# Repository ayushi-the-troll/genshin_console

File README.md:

# Genshin Impact Console
I've been wanting to create a console for my favorite game: Genshin Impact. For me, the keys on a keyboard are finnicky and too small for me to navigate them well. That's why I created a separate console that I can use for the game.

It can also be programmed for other games on PC that use the keyboard to perform actions. It has up to five action-buttons that you can use!

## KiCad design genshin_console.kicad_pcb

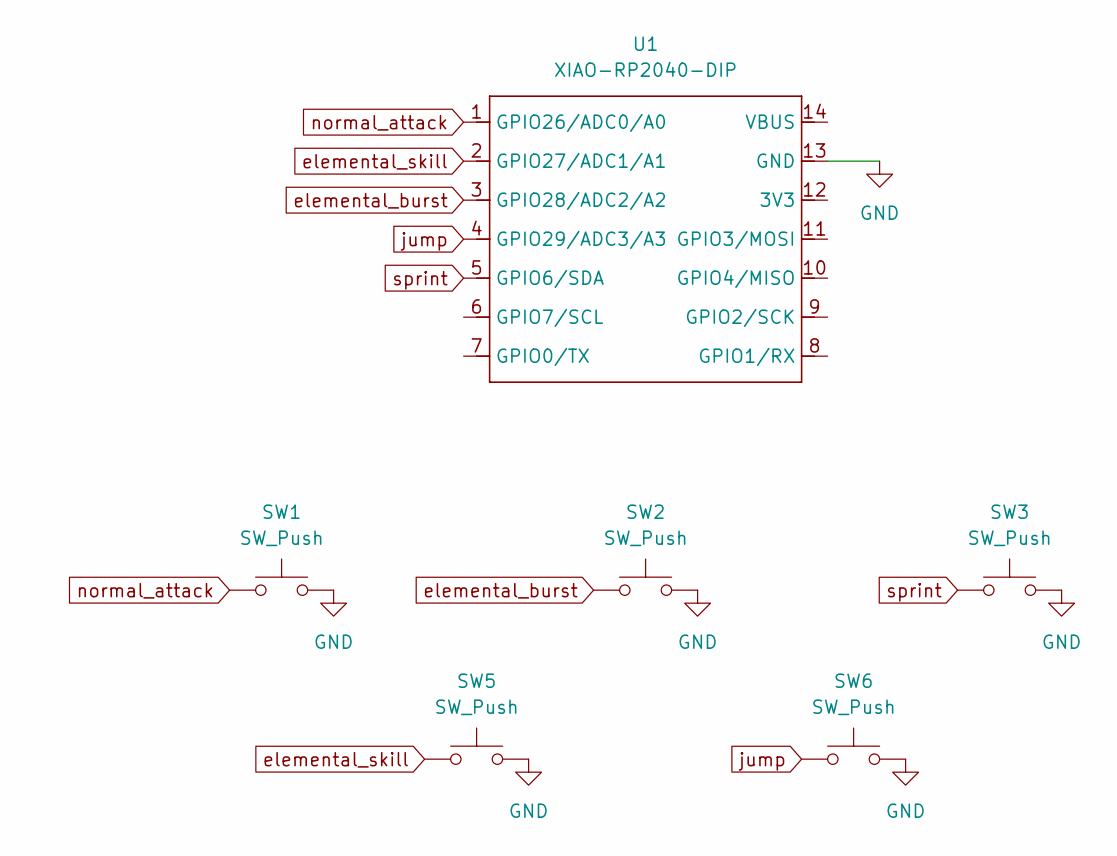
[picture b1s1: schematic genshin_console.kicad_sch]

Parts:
SW1, SW2, SW3, SW5, SW6: SW_Push; SW_Cherry_MX_1.00u_PCB
U1: XIAO-RP2040-DIP; XIAO-RP2040-DIP (1)

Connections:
GND: SW1.2, SW2.2, SW3.2, SW5.2, SW6.2, U1.13 (GND)
elemental_burst: SW2.1, U1.3 (GPIO28/ADC2/A2)
elemental_skill: SW5.1, U1.2 (GPIO27/ADC1/A1)
jump: SW6.1, U1.4 (GPIO29/ADC3/A3)
normal_attack: SW1.1, U1.1 (GPIO26/ADC0/A0)
sprint: SW3.1, U1.5 (GPIO6/SDA)

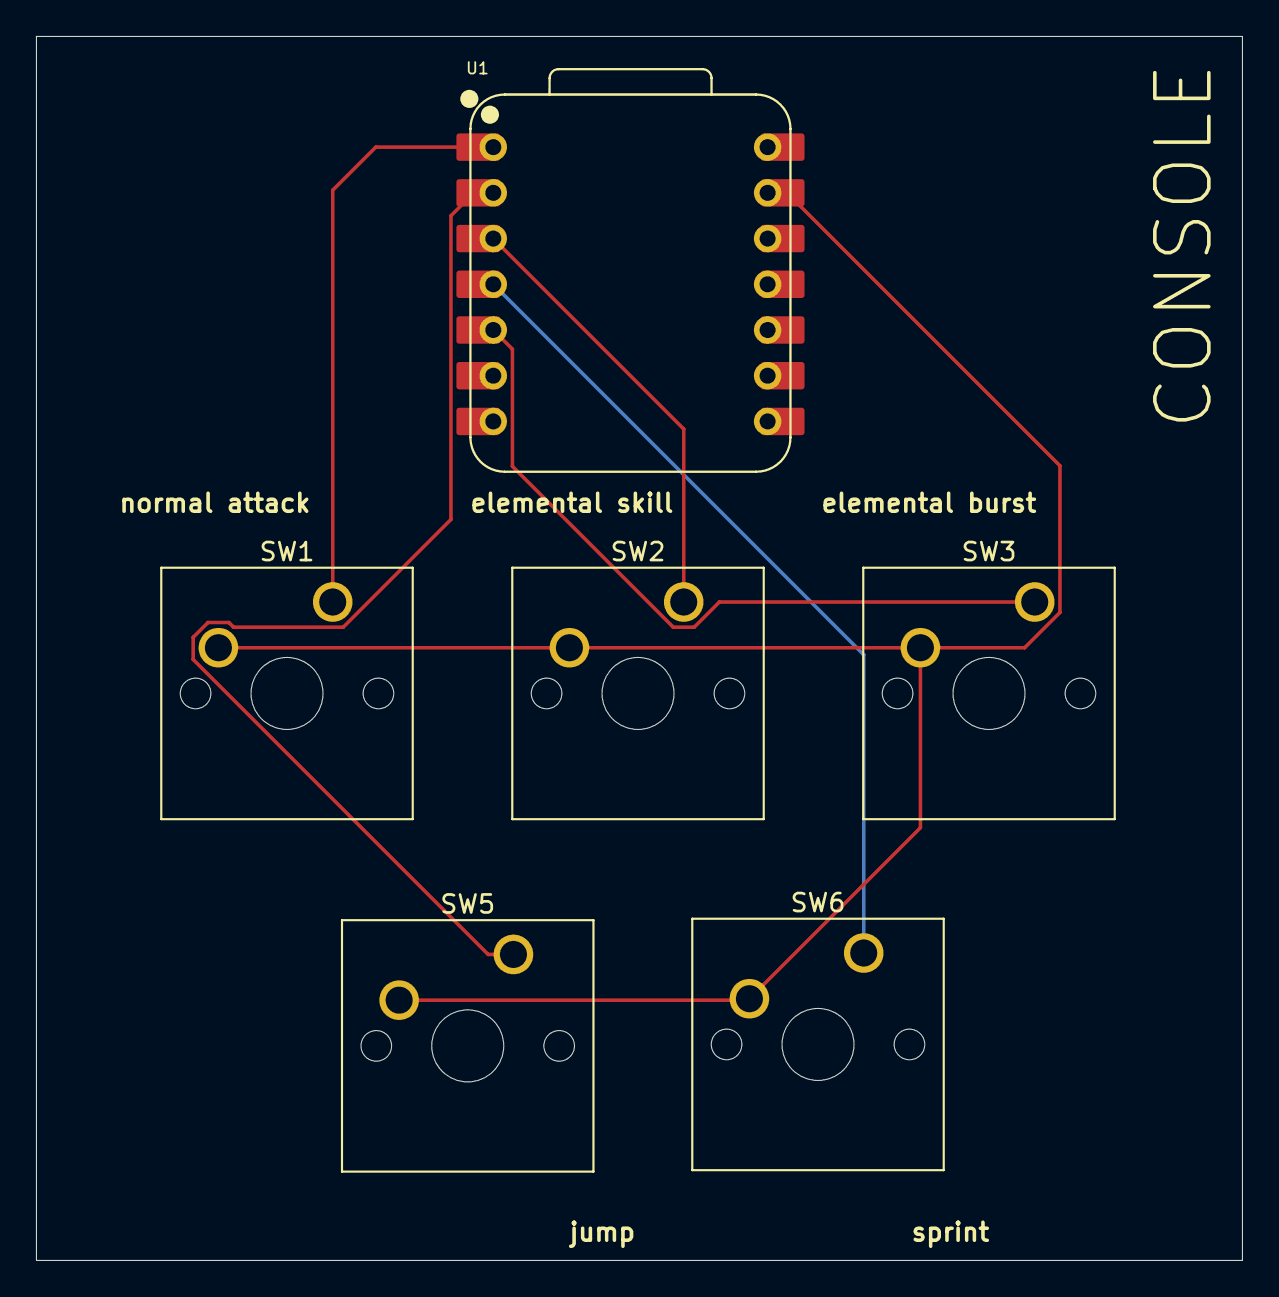
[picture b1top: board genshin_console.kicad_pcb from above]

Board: 2 copper layers, 67.0 x 68.0 mm, 6 parts (0 on the bottom side), 6 nets.

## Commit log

2025-07-20 Added gerber and drill files
2025-07-21 Added STL file of cadded case
